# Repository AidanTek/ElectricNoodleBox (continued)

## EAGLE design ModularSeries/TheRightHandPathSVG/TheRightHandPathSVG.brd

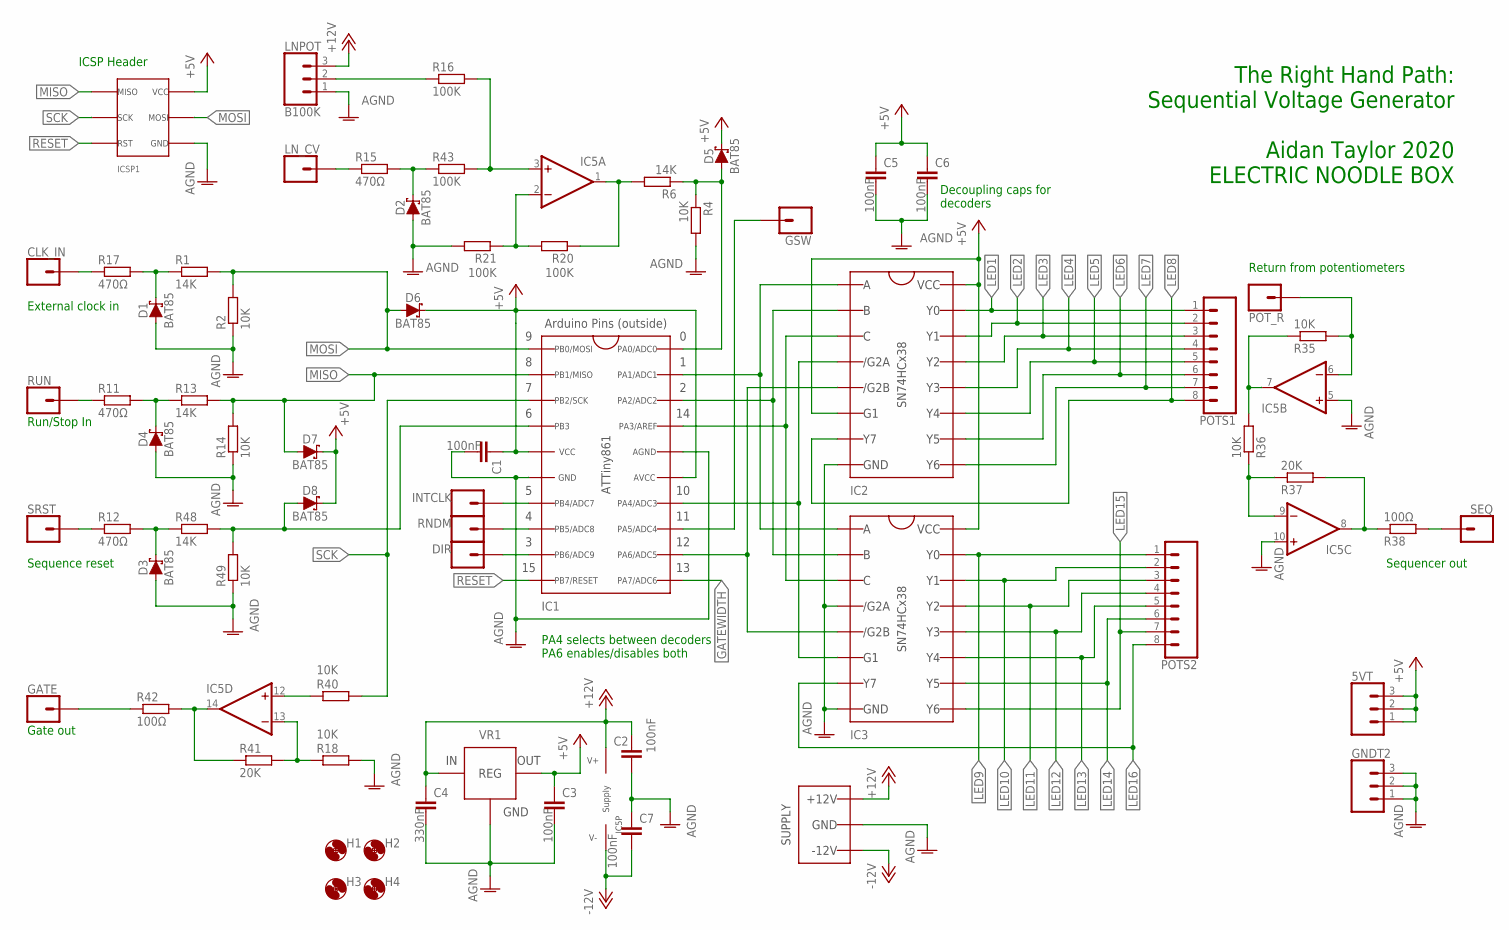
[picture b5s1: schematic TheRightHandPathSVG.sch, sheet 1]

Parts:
5VT: 3XWIREPAD; 1X03
C1, C2, C3, C5, C6, C7: 100nF; C050-025X075
C4: 330nF; C050-025X075
CLK_IN: 1XWIREPAD; 1X01
D1, D2, D3, D4, D5, D6, D7, D8: BAT85; DO35-7
DIR: 1XWIREPAD; 1X01
GATE: 1XWIREPAD; 1X01
GNDT2: 3XWIREPAD; 1X03
GSW: 1XWIREPAD; 1X01
H1, H2, H3, H4: MOUNT-HOLE3.2; 3,2
IC1: ATTINY861; DIL20
IC2, IC3: SN74HCX38; DIL16
IC5: TL0X4DIL; DIL14
ICSP1: ICSP_2.54; 2X3
INTCLK: 1XWIREPAD; 1X01
LNPOT: B100K; 1X03
LN_CV: 1XWIREPAD; 1X01
POTS1, POTS2: 8XWIREPAD; 1X08
POT_R: 1XWIREPAD; 1X01
R1, R6, R13, R48: 14K; 0207/10
R2, R4, R14, R18, R35, R36, R40, R49: 10K; 0207/10
R11, R12, R15, R17: 470Ω; 0207/10
R16, R20, R21, R43: 100K; 0207/10
R37, R41: 20K; 0207/10
R38, R42: 100Ω; 0207/10
RNDM: 1XWIREPAD; 1X01
RUN: 1XWIREPAD; 1X01
SEQ: 1XWIREPAD; 1X01
SRST: 1XWIREPAD; 1X01
VR1: L78L05TO92; TO92
WP1: COMBO_SUPPLY_HEADER; COMBINED_POWER

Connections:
+5V: 5VT.1, 5VT.2, 5VT.3, C1.1, C3.1, C5.1, C6.1, D5.C, D6.C, D7.C, D8.C, IC1.5 (VCC), IC1.15 (AVCC), IC2.6 (6_G1), IC2.16 (16_VCC), IC3.16 (16_VCC), ICSP1.2 (6VCC), VR1.1 (VOUT); also elsewhere on the board
+12V: C2.1, C4.1, IC5.4 (V+), LNPOT.3, VR1.3 (VIN), WP1.V+1 (V++), WP1.V+2 (V++), WP1.V+3 (V++); also elsewhere on the board
-12V: C7.2, IC5.11 (V-), WP1.V-1 (V--), WP1.V-2 (V--), WP1.V-3 (V--)
AGND: C1.2, C2.2, C3.2, C4.2, C5.2, C6.2, C7.1, D1.A, D2.A, D3.A, D4.A, GNDT2.1, GNDT2.2, GNDT2.3, IC1.6 (GND), IC1.16 (AGND), IC2.8 (8_GND), IC3.4 (4_/G2A), IC3.8 (8_GND), IC5.5 (+IN), IC5.10 (+IN), ICSP1.6 (4GND), LNPOT.1, R2.1, R4.2, R14.1, R18.2, R21.2, R49.1, VR1.2 (GND), WP1.GND1 (AGND), WP1.GND2 (AGND), WP1.GND3 (AGND), WP1.GND4 (AGND), WP1.GND5 (AGND), WP1.GND6 (AGND), WP1.GND7 (AGND), WP1.GND8 (AGND); also elsewhere on the board
GATEWIDTH: IC1.11 (11_PA7)
LED1: IC2.15 (15_Y0), POTS1.1; also elsewhere on the board
LED2: IC2.14 (14_Y1), POTS1.2; also elsewhere on the board
LED3: IC2.13 (13_Y2), POTS1.3; also elsewhere on the board
LED4: IC2.12 (12_Y3), POTS1.4; also elsewhere on the board
LED5: IC2.11 (11_Y4), POTS1.5; also elsewhere on the board
LED6: IC2.10 (10_Y5), POTS1.6; also elsewhere on the board
LED7: IC2.9 (9_Y6), POTS1.7; also elsewhere on the board
LED8: IC2.7 (7_Y7), POTS1.8; also elsewhere on the board
LED9: IC3.15 (15_Y0), POTS2.1; also elsewhere on the board
LED10: IC3.14 (14_Y1), POTS2.2; also elsewhere on the board
LED11: IC3.13 (13_Y2), POTS2.3; also elsewhere on the board
LED12: IC3.12 (12_Y3), POTS2.4; also elsewhere on the board
LED13: IC3.11 (11_Y4), POTS2.5; also elsewhere on the board
LED14: IC3.10 (10_Y5), POTS2.6; also elsewhere on the board
LED15: IC3.9 (9_Y6), POTS2.7; also elsewhere on the board
LED16: IC3.7 (7_Y7), POTS2.8; also elsewhere on the board
MISO: D7.A, IC1.2 (2_PB1), ICSP1.1 (1MISO), R13.2, R14.2
MOSI: D6.A, IC1.1 (1_PB0), ICSP1.4 (5MOSI), R1.2, R2.2
N2V5REF: IC5.2 (-IN), R20.2, R21.1
unnamed: IC1.14 (14_PA4), IC2.4 (4_/G2A), IC3.6 (6_G1)
unnamed: IC1.17 (17_PA3), IC2.3 (3_C), IC3.3 (3_C)
unnamed: IC1.18 (18_PA2), IC2.2 (2_B), IC3.2 (2_B)
unnamed: IC1.19 (19_PA1), IC2.1 (1_A), IC3.1 (1_A)
unnamed: D4.C, R11.2, R13.1
unnamed: GSW.1, IC1.13 (13_PA5)
unnamed: D1.C, R1.1, R17.2
unnamed: D2.C, R15.2, R43.1
unnamed: IC1.7 (7_PB4), INTCLK.1
unnamed: IC1.12 (12_PA6), IC2.5 (5_/G2B), IC3.5 (5_/G2B)
unnamed: IC5.1 (OUT), R6.2, R20.1
unnamed: D5.A, IC1.20 (20_PA0), R4.1, R6.1
unnamed: R11.1, RUN.1
unnamed: D3.C, R12.2, R48.1
unnamed: LN_CV.1, R15.1
unnamed: R12.1, SRST.1
unnamed: LNPOT.2, R16.1
unnamed: CLK_IN.1, R17.1
unnamed: IC5.14 (OUT), R41.1, R42.2
unnamed: IC5.13 (-IN), R18.1, R41.2
unnamed: IC5.6 (-IN), POT_R.1, R35.2
unnamed: IC5.7 (OUT), R35.1, R36.2
unnamed: IC5.9 (-IN), R36.1, R37.1
unnamed: R38.2, SEQ.1
unnamed: IC5.8 (OUT), R37.2, R38.1
unnamed: IC5.12 (+IN), R40.1
unnamed: GATE.1, R42.1
unnamed: IC5.3 (+IN), R16.2, R43.2
unnamed: IC1.8 (8_PB5), RNDM.1
unnamed: DIR.1, IC1.9 (9_PB6)
unnamed: D8.A, IC1.4 (4_PB3), R48.2, R49.2
RESET: IC1.10 (10_PB7), ICSP1.5 (3RST)
SCK: IC1.3 (3_PB2), ICSP1.3 (2SCK), R40.2

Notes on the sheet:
Decoupling caps for decoders
Sequence reset
External clock in
Sequencer out
Return from potentiometers
The Right Hand Path: Sequential Voltage Generator Aidan Taylor 2020 ELECTRIC NOODLE BOX
ICSP Header
Gate out
Run/Stop In
PA4 selects between decoders PA6 enables/disables both

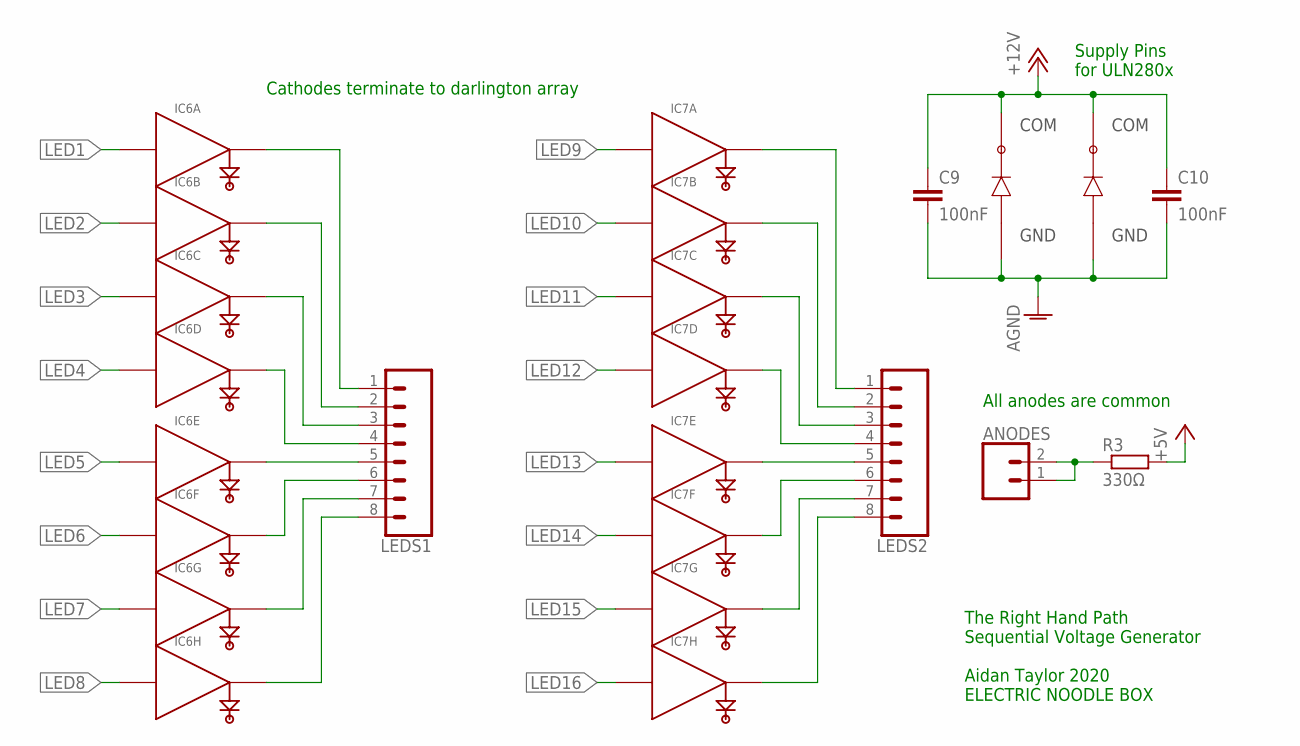
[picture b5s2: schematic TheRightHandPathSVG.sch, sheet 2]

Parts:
ANODES: 2XWIREPAD; 1X02
C9, C10: 100nF; C050-025X075
IC6, IC7: ULN2801; DIL18
LEDS1, LEDS2: 8XWIREPAD; 1X08
R3: 330Ω; 0207/10

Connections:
+5V: R3.2; also elsewhere on the board
+12V: C9.1, C10.1, IC6.10 (COM), IC7.10 (COM); also elsewhere on the board
AGND: C9.2, C10.2, IC6.9 (GND), IC7.9 (GND); also elsewhere on the board
LED1: IC6.1 (IN); also elsewhere on the board
LED2: IC6.2 (IN); also elsewhere on the board
LED3: IC6.3 (IN); also elsewhere on the board
LED4: IC6.4 (IN); also elsewhere on the board
LED5: IC6.5 (IN); also elsewhere on the board
LED6: IC6.6 (IN); also elsewhere on the board
LED7: IC6.7 (IN); also elsewhere on the board
LED8: IC6.8 (IN); also elsewhere on the board
LED9: IC7.1 (IN); also elsewhere on the board
LED10: IC7.2 (IN); also elsewhere on the board
LED11: IC7.3 (IN); also elsewhere on the board
LED12: IC7.4 (IN); also elsewhere on the board
LED13: IC7.5 (IN); also elsewhere on the board
LED14: IC7.6 (IN); also elsewhere on the board
LED15: IC7.7 (IN); also elsewhere on the board
LED16: IC7.8 (IN); also elsewhere on the board
unnamed: ANODES.1, ANODES.2, R3.1
unnamed: IC6.18, LEDS1.1
unnamed: IC6.17, LEDS1.2
unnamed: IC6.16, LEDS1.3
unnamed: IC6.15, LEDS1.4
unnamed: IC6.14, LEDS1.5
unnamed: IC6.13, LEDS1.6
unnamed: IC6.12, LEDS1.7
unnamed: IC6.11, LEDS1.8
unnamed: IC7.18, LEDS2.1
unnamed: IC7.17, LEDS2.2
unnamed: IC7.16, LEDS2.3
unnamed: IC7.15, LEDS2.4
unnamed: IC7.14, LEDS2.5
unnamed: IC7.13, LEDS2.6
unnamed: IC7.12, LEDS2.7
unnamed: IC7.11, LEDS2.8

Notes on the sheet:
The Right Hand Path Sequential Voltage Generator Aidan Taylor 2020 ELECTRIC NOODLE BOX
All anodes are common
Cathodes terminate to darlington array
Supply Pins for ULN280x

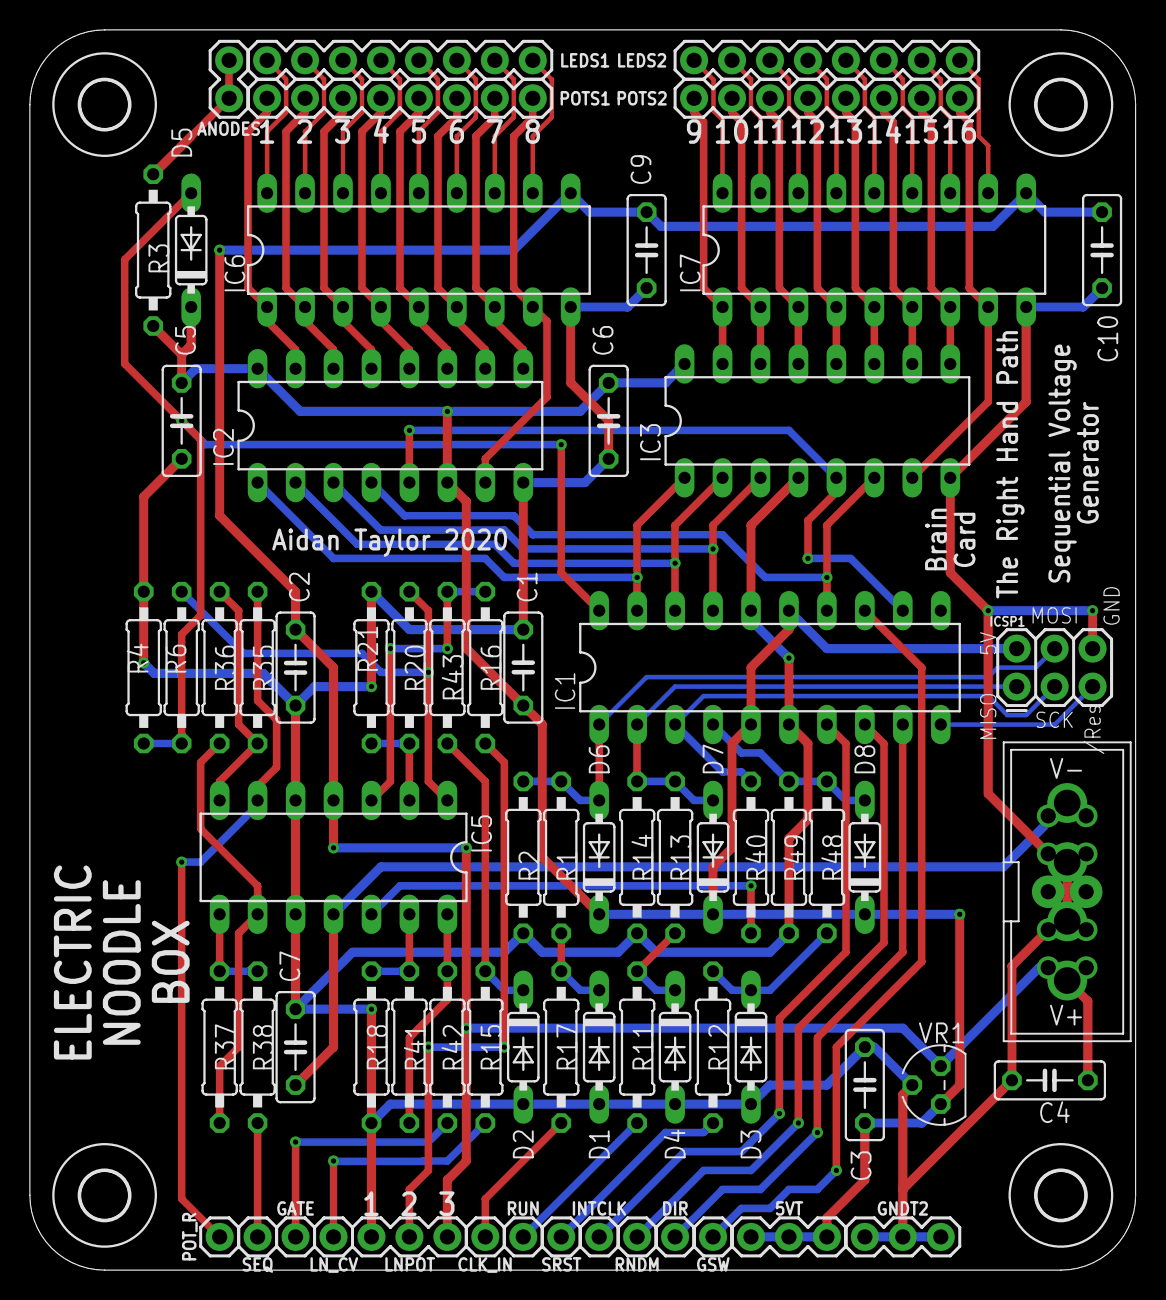
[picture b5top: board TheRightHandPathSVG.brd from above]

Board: 2 copper layers, 74.0 x 83.0 mm, 74 parts (0 on the bottom side), 73 nets.

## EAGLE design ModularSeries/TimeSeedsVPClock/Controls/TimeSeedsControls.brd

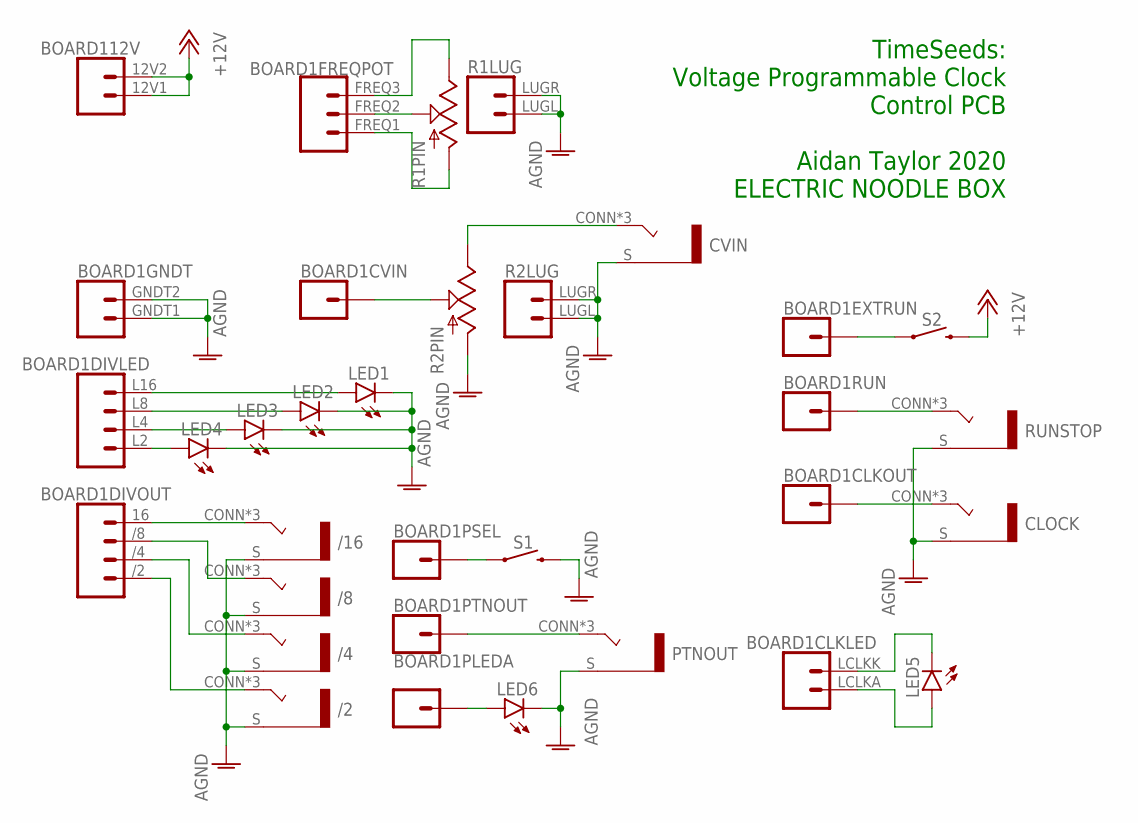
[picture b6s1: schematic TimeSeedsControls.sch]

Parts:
/2, /4, /8, /16: COMBI-JACKCINCHNANA; NEWCOMBOJACK_PANEL
BOARD1: TS-VPC_LINK; TS-VPC
CLOCK: COMBI-JACKCINCHNANA; NEWCOMBOJACK_PANEL
CVIN: COMBI-JACKCINCHNANA; NEWCOMBOJACK_PANEL
LED1, LED2, LED3, LED4, LED5, LED6: LED3MM
PTNOUT: COMBI-JACKCINCHNANA; NEWCOMBOJACK_PANEL
R1, R2: POTENTIOMETER; ALPHA_RV09_9MMPOT
RUNSTOP: COMBI-JACKCINCHNANA; NEWCOMBOJACK_PANEL
S1, S2: MCDTS-2_PUSHBUTTON

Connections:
+12V: BOARD1.12V1 (1), BOARD1.12V2 (2), S2.P$3 (2), S2.P$4 (2)
AGND: /2.S, /4.S, /8.S, /16.S, BOARD1.GNDT1 (1), BOARD1.GNDT2 (2), CLOCK.S, CVIN.S, LED1.K (C), LED2.K (C), LED3.K (C), LED4.K (C), LED6.K (C), PTNOUT.S, R1.LUGL (1), R1.LUGR (2), R2.C1 (A), R2.LUGL (1), R2.LUGR (2), RUNSTOP.S, S1.P$3 (2), S1.P$4 (2)
unnamed: BOARD1.L2 (1), LED4.A
unnamed: BOARD1.L4 (2), LED3.A
unnamed: BOARD1.L8 (3), LED2.A
unnamed: BOARD1.L16 (4), LED1.A
unnamed: /16.CONN (T), /16.T1 (T), /16.T2 (T), BOARD1.16 (4)
unnamed: /8.CONN (T), /8.T1 (T), /8.T2 (T), BOARD1./8 (3)
unnamed: /4.CONN (T), /4.T1 (T), /4.T2 (T), BOARD1./4 (2)
unnamed: /2.CONN (T), /2.T1 (T), /2.T2 (T), BOARD1./2 (1)
unnamed: BOARD1.CLK (1), CLOCK.CONN (T), CLOCK.T1 (T), CLOCK.T2 (T)
unnamed: BOARD1.LCLKA (1), LED5.A
unnamed: BOARD1.LCLKK (2), LED5.K (C)
unnamed: BOARD1.FREQ2 (2), R1.C2 (W)
unnamed: BOARD1.FREQ1 (1), R1.C1 (A)
unnamed: BOARD1.CVIN (1), R2.C2 (W)
unnamed: BOARD1.FREQ3 (3), R1.C3 (B)
unnamed: CVIN.CONN (T), CVIN.T1 (T), CVIN.T2 (T), R2.C3 (B)
unnamed: BOARD1.PTRNOUT (1), PTNOUT.CONN (T), PTNOUT.T1 (T), PTNOUT.T2 (T)
unnamed: BOARD1.PLEDA (1), LED6.A
unnamed: BOARD1.PSEL (1), S1.P$1 (1), S1.P$2 (1)
unnamed: BOARD1.EXTRUN (1), S2.P$1 (1), S2.P$2 (1)
unnamed: BOARD1.RUN (1), RUNSTOP.CONN (T), RUNSTOP.T1 (T), RUNSTOP.T2 (T)

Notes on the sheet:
TimeSeeds: Voltage Programmable Clock Control PCB Aidan Taylor 2020 ELECTRIC NOODLE BOX

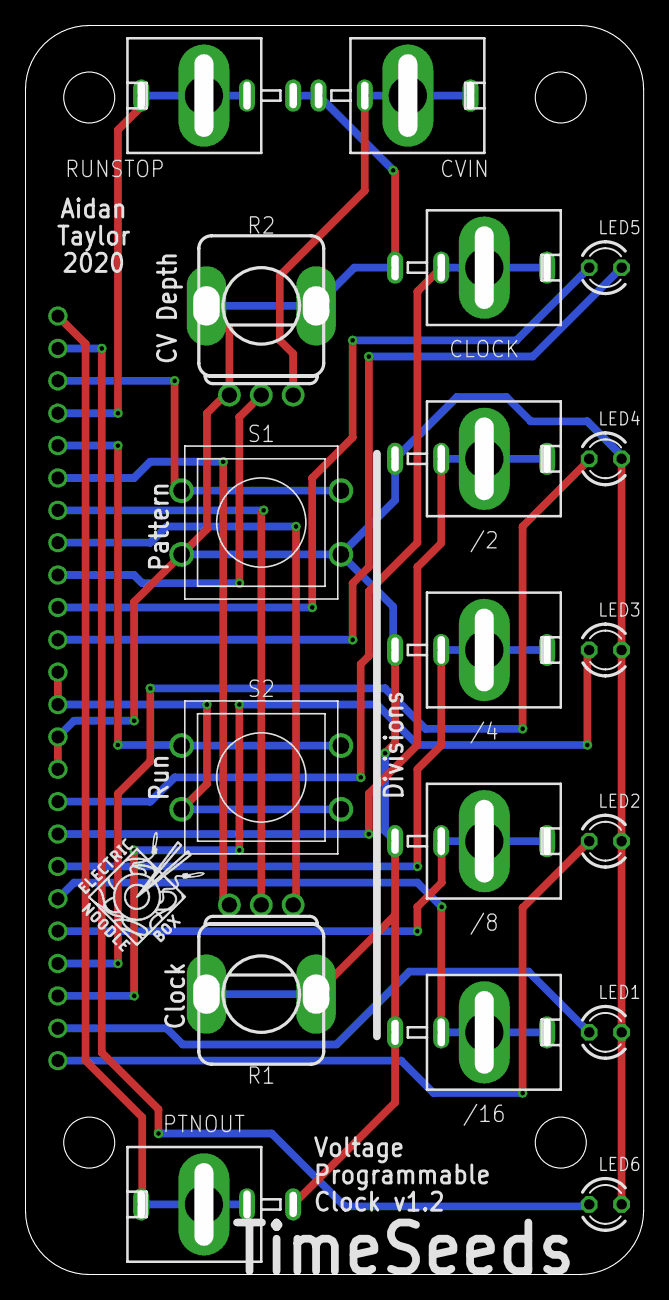
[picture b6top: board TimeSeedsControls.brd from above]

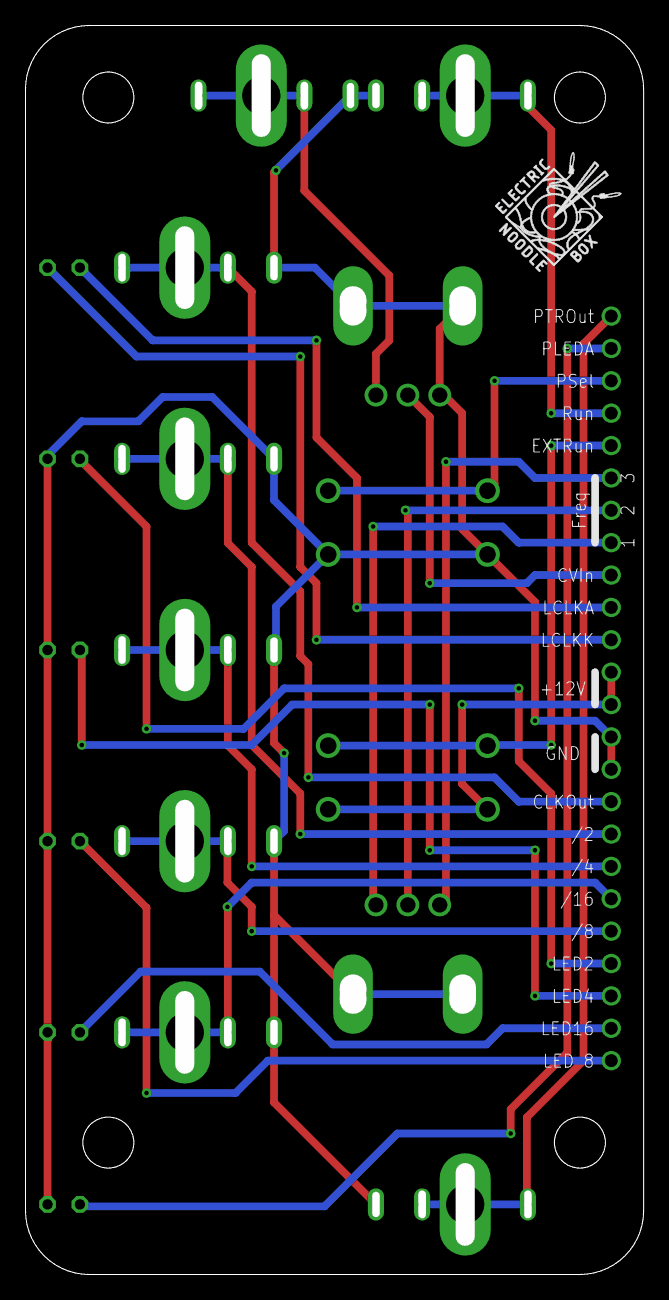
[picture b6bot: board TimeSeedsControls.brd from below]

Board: 2 copper layers, 48.5 x 98.0 mm, 21 parts (2 on the bottom side), 23 nets.

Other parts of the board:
U$1, U$2: LOGO10X10
